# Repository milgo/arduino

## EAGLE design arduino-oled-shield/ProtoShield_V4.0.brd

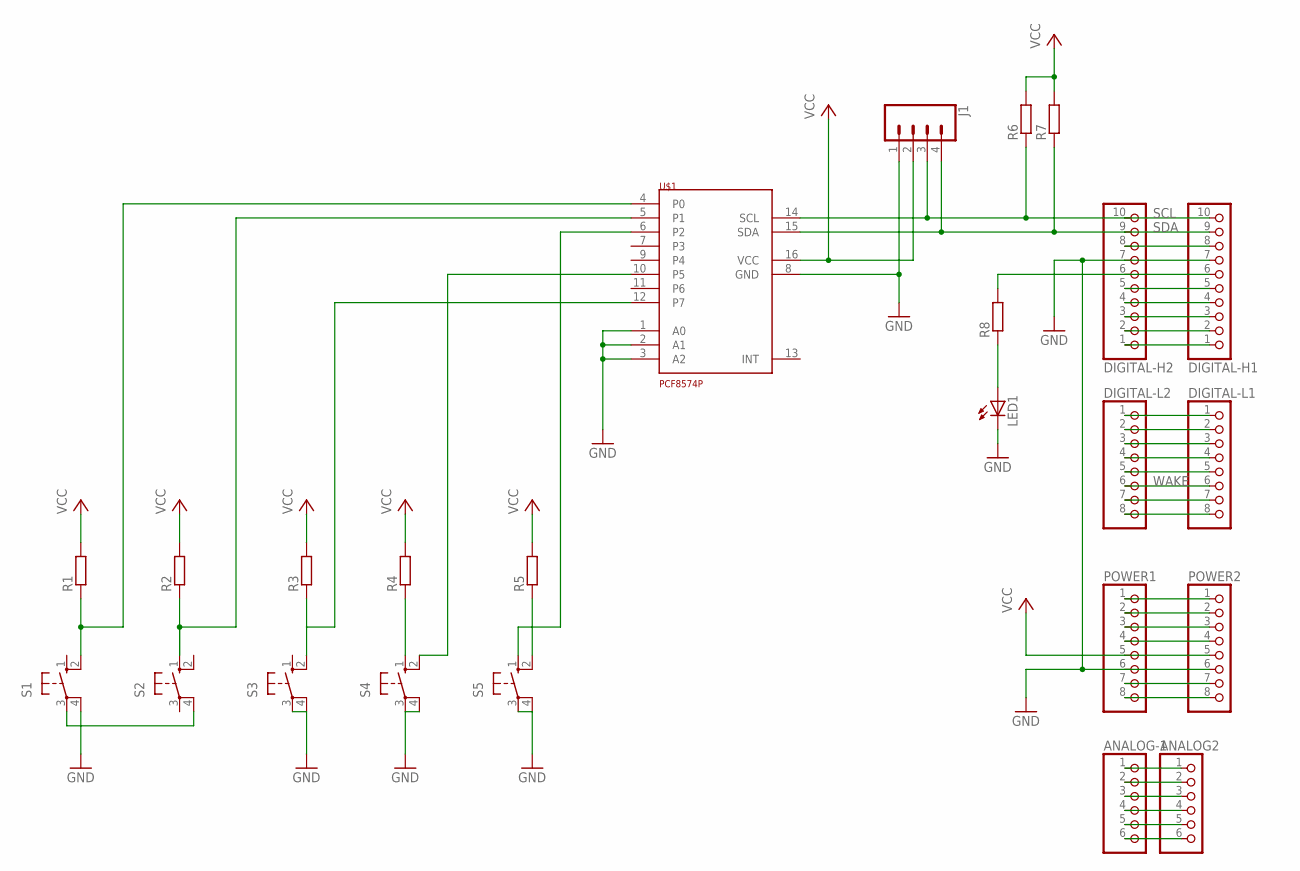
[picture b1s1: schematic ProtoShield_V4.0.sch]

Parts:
ANALOG2: PINHD-1X6; 1X06
ANALOG-1: PINHD-1X6; 1X06
DIGITAL-H1, DIGITAL-H2: PINHD-1X10TH; 1X10-TH
DIGITAL-L1, DIGITAL-L2: PINHD-1X8; 1X08; MPN B67345B0001X087
J1: CONN_04PTH; 1X04
LED1: LED3MM
POWER1, POWER2: PINHD-1X8TH; 1X08-TH
R1, R2, R3, R4, R5, R6, R7, R8: R-EU_0207/10; 0207/10
S1, S2, S3, S4, S5: 10-XX; B3F-10XX
U$1: PCF8574P; DIL16

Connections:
GND: DIGITAL-H1.7, DIGITAL-H2.7, J1.1, LED1.K (C), POWER1.6, POWER2.6, S1.4 (P1), S3.3, S3.4 (P1), S4.3, S4.4 (P1), S5.3, S5.4 (P1), U$1.1 (A0), U$1.2 (A1), U$1.3 (A2), U$1.8 (GND)
IOREF: POWER1.2, POWER2.2
unnamed: DIGITAL-H1.6, DIGITAL-H2.6, R8.2
unnamed: DIGITAL-H1.1, DIGITAL-H2.1
unnamed: DIGITAL-H1.4, DIGITAL-H2.4
unnamed: DIGITAL-H1.5, DIGITAL-H2.5
unnamed: R2.1, S2.1 (S), U$1.5 (P1)
unnamed: DIGITAL-H1.2, DIGITAL-H2.2
unnamed: DIGITAL-H1.3, DIGITAL-H2.3
unnamed: DIGITAL-L1.1, DIGITAL-L2.1
unnamed: DIGITAL-L1.2, DIGITAL-L2.2
unnamed: DIGITAL-L1.3, DIGITAL-L2.3
unnamed: DIGITAL-L1.4, DIGITAL-L2.4
unnamed: DIGITAL-L1.5, DIGITAL-L2.5
unnamed: POWER1.7, POWER2.7
unnamed: DIGITAL-L1.7, DIGITAL-L2.7
unnamed: DIGITAL-L1.8, DIGITAL-L2.8
unnamed: S1.3, S2.4 (P1)
unnamed: R1.1, S1.2 (S1), U$1.4 (P0)
unnamed: ANALOG2.1, ANALOG-1.1
unnamed: ANALOG2.2, ANALOG-1.2
unnamed: ANALOG2.3, ANALOG-1.3
unnamed: ANALOG2.4, ANALOG-1.4
unnamed: ANALOG2.5, ANALOG-1.5
unnamed: ANALOG2.6, ANALOG-1.6
unnamed: LED1.A, R8.1
unnamed: R3.1, S3.2 (S1), U$1.12 (P7)
unnamed: POWER1.3, POWER2.3
unnamed: POWER1.8, POWER2.8
unnamed: R4.1, S4.1 (S)
unnamed: R5.1, S5.2 (S1)
unnamed: POWER1.1, POWER2.1
unnamed: S4.2 (S1), U$1.10 (P5)
unnamed: POWER1.4, POWER2.4
unnamed: S5.1 (S), U$1.6 (P2)
unnamed: DIGITAL-H1.8, DIGITAL-H2.8
SCL: DIGITAL-H1.10, DIGITAL-H2.10, J1.3, R6.1, U$1.14 (SCL)
SDA: DIGITAL-H1.9, DIGITAL-H2.9, J1.4, R7.1, U$1.15 (SDA)
VCC: J1.2, POWER1.5, POWER2.5, R1.2, R2.2, R3.2, R4.2, R5.2, R6.2, R7.2, U$1.16 (VCC)
WAKE: DIGITAL-L1.6, DIGITAL-L2.6

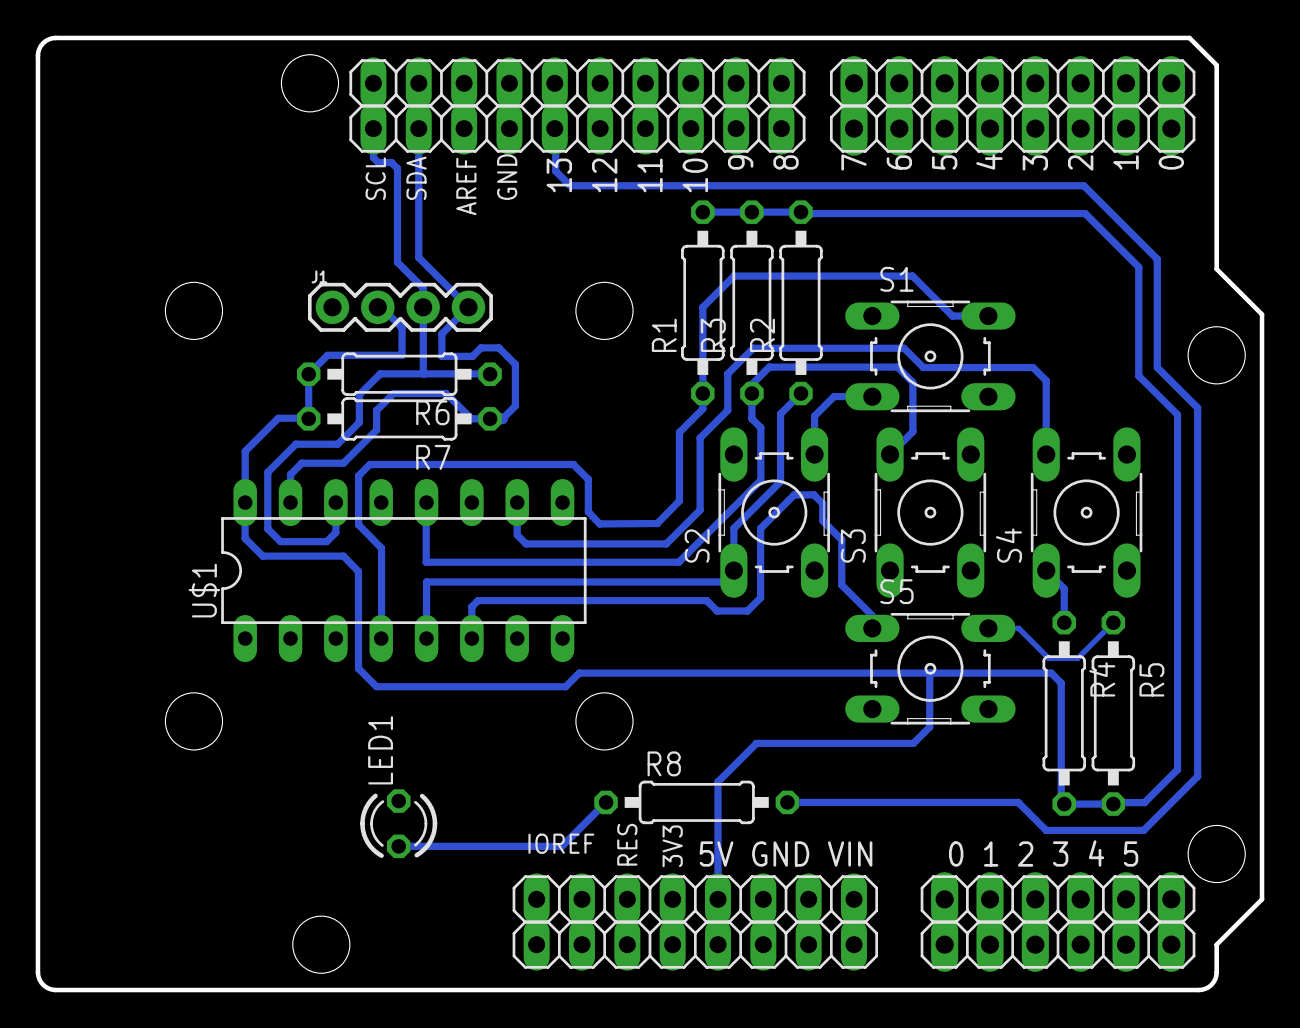
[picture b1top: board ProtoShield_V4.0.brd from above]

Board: 2 copper layers, 68.6 x 53.3 mm, 24 parts (0 on the bottom side), 40 nets.

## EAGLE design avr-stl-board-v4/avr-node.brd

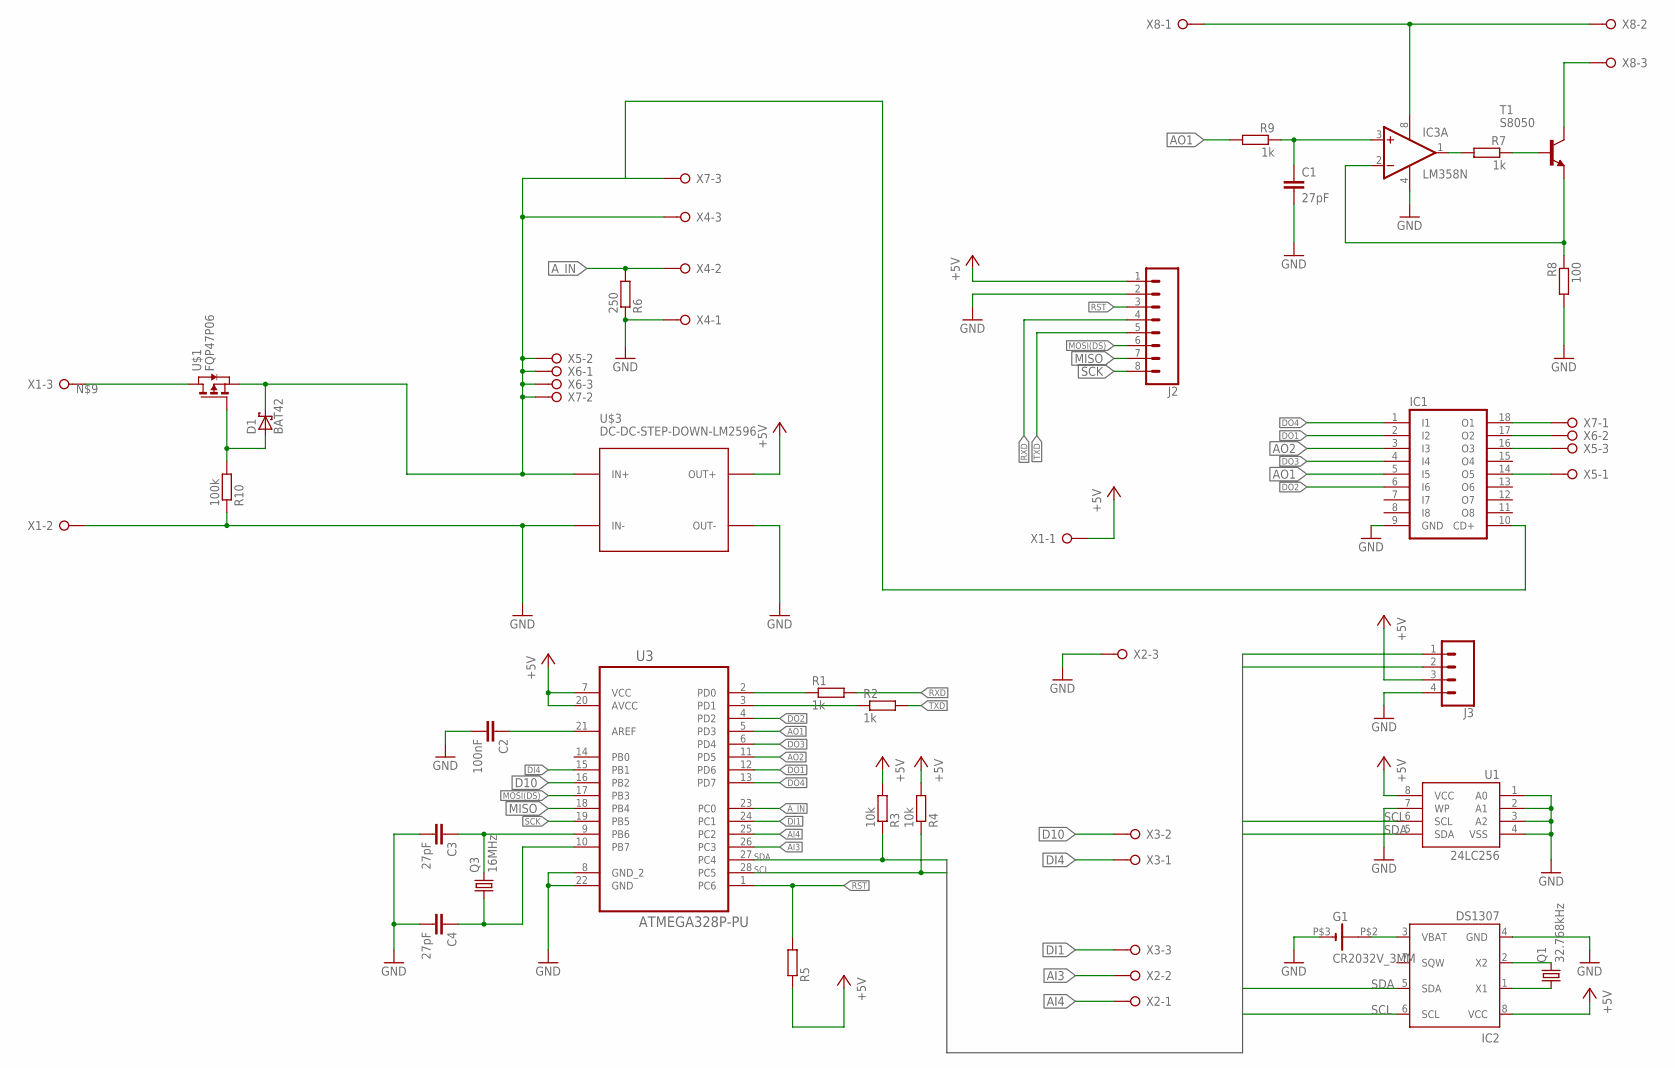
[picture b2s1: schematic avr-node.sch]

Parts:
C1, C3, C4: 27pF; C050-025X075
C2: 100nF; C050-025X075
D1: BAT42; DO35-10
G1: CR2032V_3MM
IC1: ULN2803A; DIL18
IC2: DS1307; DIL08
IC3: LM358N; DIL08
J2: CONN_08LONGPADS; 1X08_LONGPADS
J3: CONN_04PTH; 1X04
Q1: 32.768kHz; TC26V
Q3: 16MHz; HC49U-V
R1, R2, R7, R9: 1k; 0204/7
R3, R4: 10k; 0204/7
R5: R-EU_0204/7; 0204/7
R6: 250; 0204/7
R8: 100; 0204/7
R10: 100k; 0204/7
T1: S8050; TO92L
U1: 24LC256; SO08
U3: ATMEGA328P-PU; DIP254P762X457-28
U$1: FQP47P06; TO220
U$3: DC-DC-STEP-DOWN-LM2596
X1, X2, X3, X4, X5, X6, X7, X8: W237-3E

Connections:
+5V: IC2.8 (VCC), J2.1, J3.3, R3.2, R4.2, R5.1, U1.8 (VCC), U3.7 (VCC), U3.20 (AVCC), U$3.OUT+, X1.1
AI3: U3.26 (PC3), X2.2
AI4: U3.25 (PC2), X2.1
AO1: IC1.5 (I5), R9.2, U3.5 (PD3)
AO2: IC1.3 (I3), U3.11 (PD5)
AO_SUP: IC3.8 (V+), X8.1, X8.2
A_IN: R6.2, U3.23 (PC0), X4.2
D10: U3.16 (PB2), X3.2
DI1: U3.24 (PC1), X3.3
DI4: U3.15 (PB1), X3.1
DO1: IC1.2 (I2), U3.12 (PD6)
DO2: IC1.6 (I6), U3.4 (PD2)
DO3: IC1.4 (I4), U3.6 (PD4)
DO4: IC1.1 (I1), U3.13 (PD7)
GND: C1.2, C2.2, C3.2, C4.2, G1.P$3 (-), IC1.9 (GND), IC2.4 (GND), IC3.4 (V-), J2.2, J3.4, R6.1, R8.2, R10.1, U1.1 (A0), U1.2 (A1), U1.3 (A2), U1.4 (VSS), U1.7 (WP), U3.8 (GND_2), U3.22 (GND), U$3.IN-, U$3.OUT-, X1.2, X2.3, X4.1
MISO: J2.7, U3.18 (PB4)
MOSI(DS): J2.6, U3.17 (PB3)
unnamed: IC3.1 (OUT), R7.2
unnamed: R7.1, T1.2 (B)
unnamed: R1.1, U3.2 (PD0)
unnamed: R2.1, U3.3 (PD1)
unnamed: T1.3 (C), X8.3
unnamed: C2.1, U3.21 (AREF)
unnamed: C3.1, Q3.2, U3.9 (PB6)
unnamed: C4.1, Q3.1, U3.10 (PB7)
unnamed: U$1.2 (D), X1.3
unnamed: IC1.16 (O3), X5.3
unnamed: IC1.17 (O2), X6.2
unnamed: IC1.14 (O5), X5.1
unnamed: IC1.18 (O1), X7.1
unnamed: IC3.2 (-IN), R8.1, T1.1 (E)
unnamed: D1.A, R10.2, U$1.1 (G)
unnamed: C1.1, IC3.3 (+IN), R9.1
unnamed: IC2.2 (X2), Q1.2
unnamed: IC2.1 (X1), Q1.1
unnamed: G1.P$2 (+), IC2.3 (VBAT)
RST: J2.3, R5.2, U3.1 (PC6)
RXD: J2.4, R1.2
SCK: J2.8, U3.19 (PB5)
SCL: IC2.6 (SCL), J3.1, R4.1, U1.6 (SCL), U3.28 (PC5)
SDA: IC2.5 (SDA), J3.2, R3.1, U1.5 (SDA), U3.27 (PC4)
TXD: J2.5, R2.2
V_IN: D1.C, IC1.10 (CD+), U$1.3 (S), U$3.IN+, X4.3, X5.2, X6.1, X6.3, X7.2, X7.3

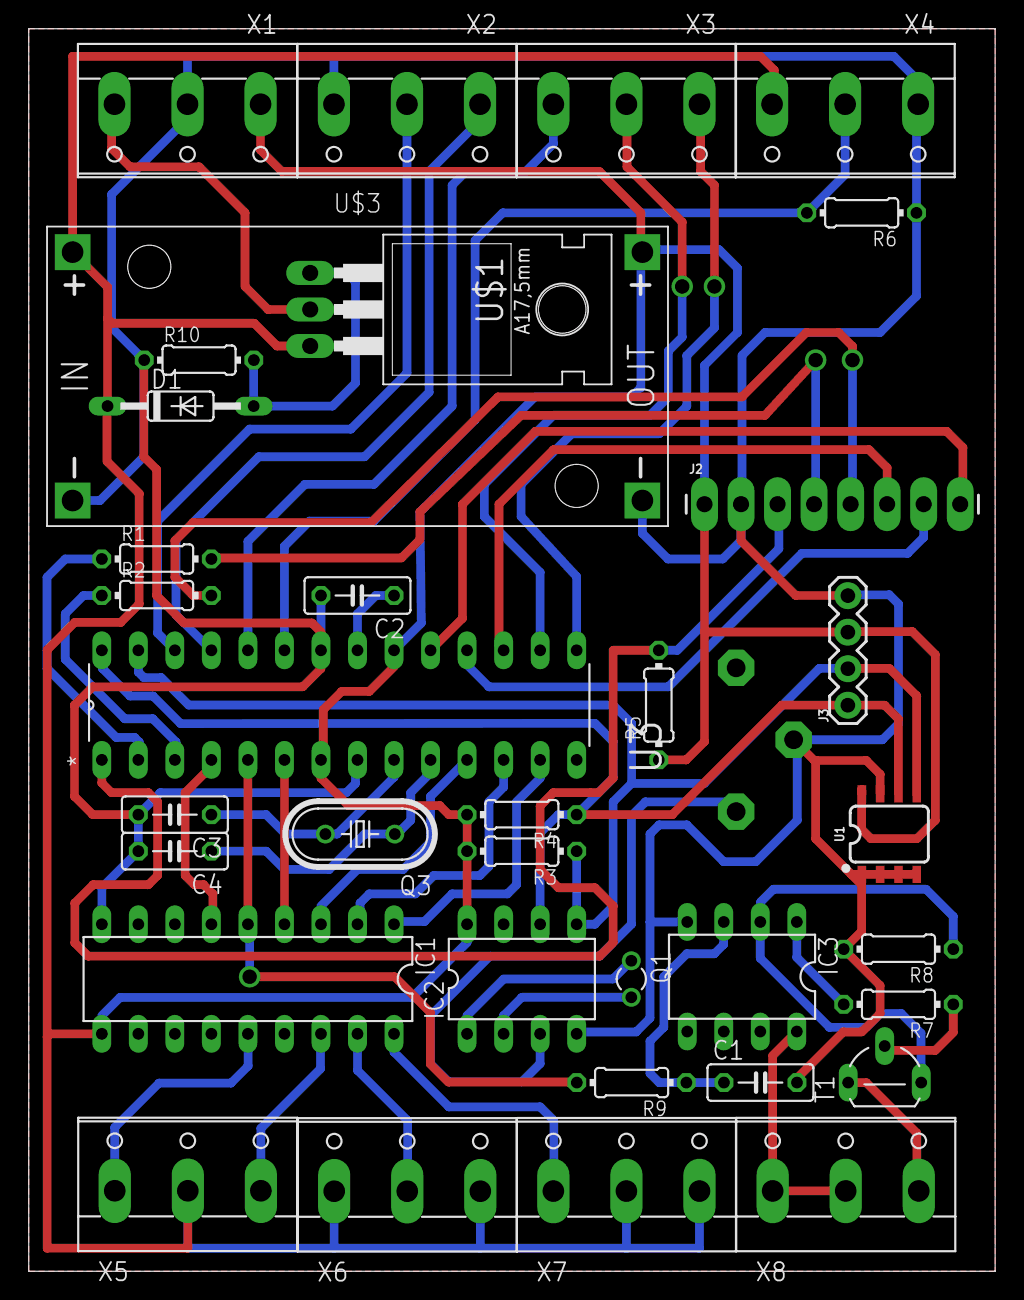
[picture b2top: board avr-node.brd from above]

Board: 2 copper layers, 67.2 x 86.4 mm, 36 parts (0 on the bottom side), 43 nets.

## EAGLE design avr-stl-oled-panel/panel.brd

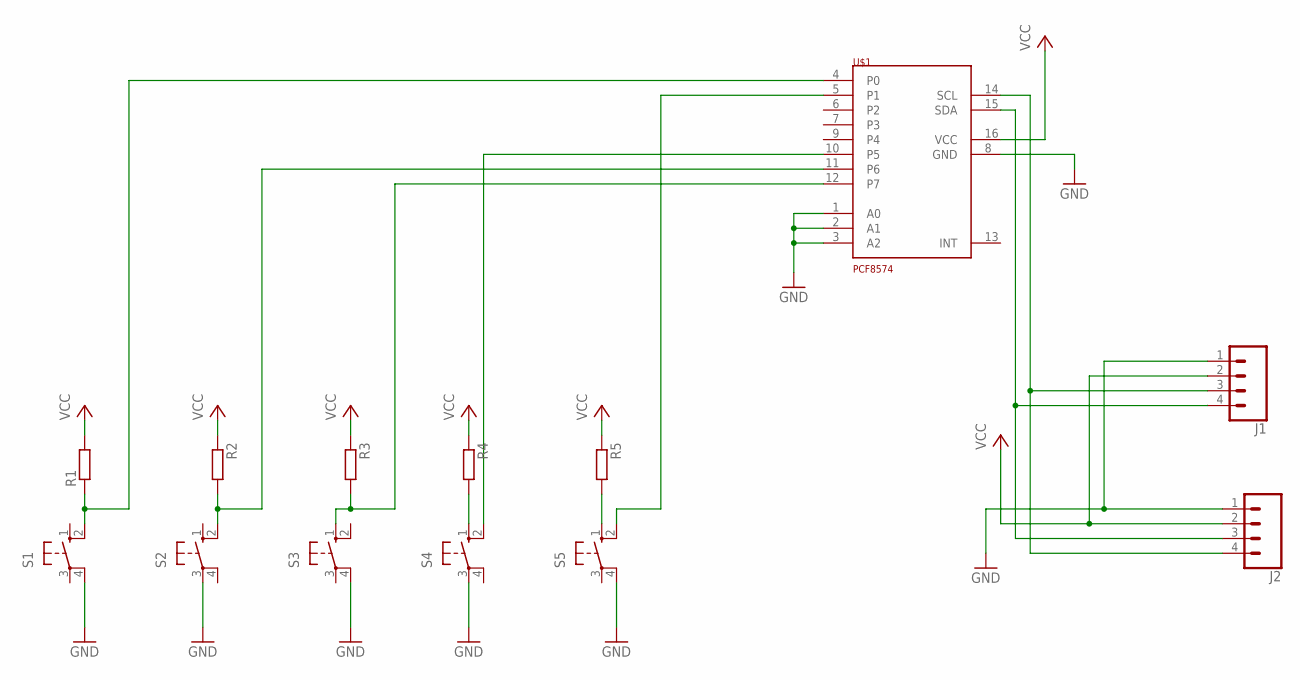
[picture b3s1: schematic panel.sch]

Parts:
J1, J2: CONN_04PTH; 1X04
R1, R2, R3, R4, R5: R-EU_0204/7; 0204/7
S1, S2, S3, S4, S5: 10-XX; B3F-10XX
U$1: PCF8574; SO16(SW)

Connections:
B0: R1.1, S1.2 (S1), U$1.4 (P0)
B1: R2.2, S2.2 (S1), U$1.11 (P6)
B2: R3.2, S3.1 (S), U$1.12 (P7)
B3: S4.2 (S1), U$1.10 (P5)
B4: S5.2 (S1), U$1.5 (P1)
GND: J1.1, J2.1, S1.4 (P1), S2.3, S3.4 (P1), S4.3, S5.4 (P1), U$1.1 (A0), U$1.2 (A1), U$1.3 (A2), U$1.8 (GND)
unnamed: R5.2, S5.1 (S)
unnamed: R4.2, S4.1 (S)
unnamed: J1.4, J2.3, U$1.15 (SDA)
unnamed: J1.3, J2.4, U$1.14 (SCL)
VCC: J1.2, J2.2, R1.2, R2.1, R3.1, R4.1, R5.1, U$1.16 (VCC)

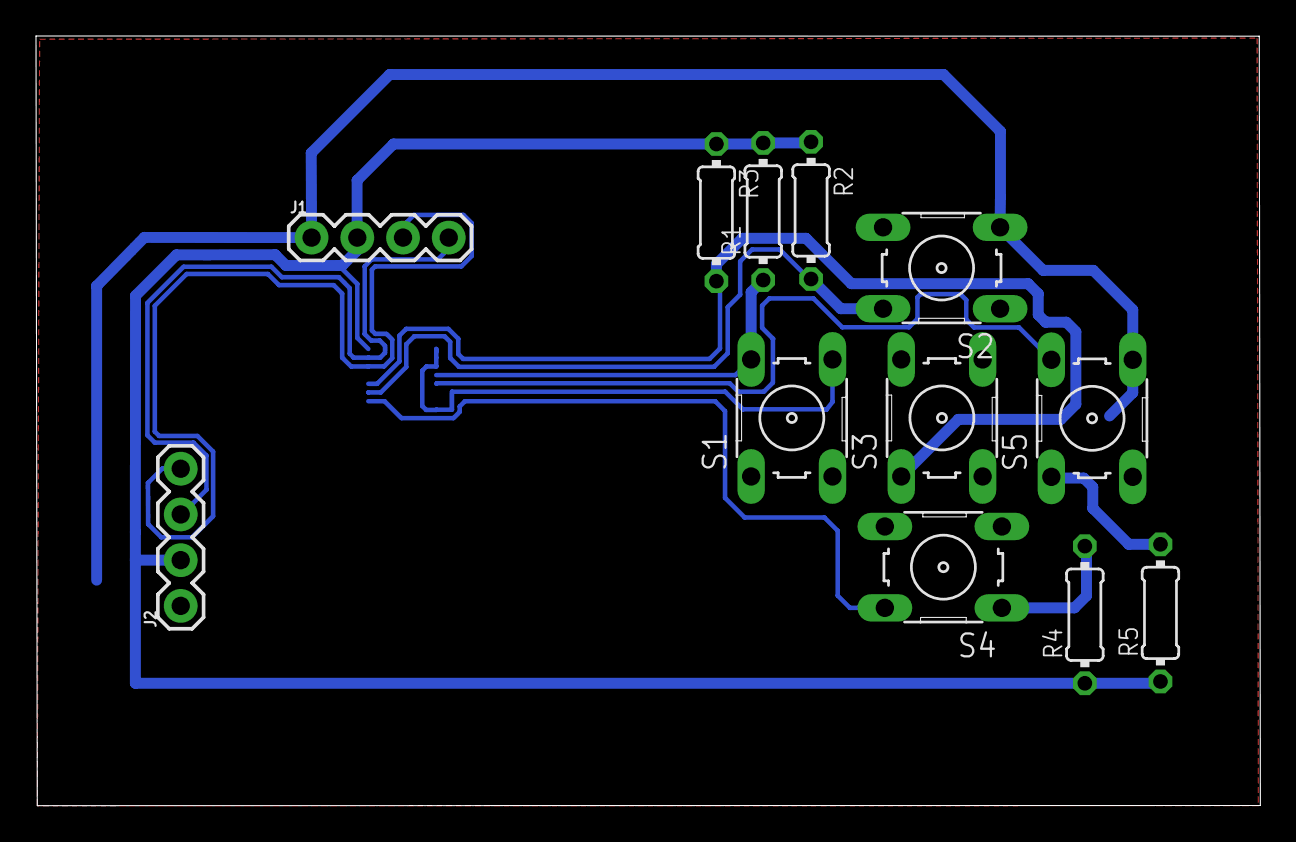
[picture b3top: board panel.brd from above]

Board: 2 copper layers, 68.0 x 42.8 mm, 13 parts (1 on the bottom side), 11 nets.

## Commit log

2021-04-22 two menus and better getButtons function
2021-04-23 single dimention menu array
2021-04-26 walking trought menu in adn out
2021-07-06 implementing function edition
2021-09-24 edit STL program step 1
2021-09-27 moving up and down in editor
2021-09-27 enter value editbox implemented
2021-09-28 advanced enter value editbox
2021-09-29 one show menu function
2021-09-29 show menu from, to feature
2021-09-29 adding move command group
2021-09-30 display msg in progmem
2021-09-30 mem menu array in progmem
2021-09-30 adding mem menu after command
2021-10-01 adding input restriction detection
2021-10-01 enter value based on mem
2021-10-01 adding new program lines
2021-10-01 adding edit menu
2021-10-01 insert, edit, remove program lines
2021-10-18 int uint command mem problem solved
2021-10-19 separating stl interpreter code
2021-10-19 separating gui
2021-10-19 PS and PC separation
2021-10-19 running program and basic testing
2021-10-20 mem organisation, assigning buttonds to I0, led to Q0.5
2021-10-21 always run, enter menu on startup, implementing some functions
2021-10-21 adding input PIND at I0, adding fp and fn basic func
2021-10-22 saving before trying new approach
2021-11-03 new way of handling memory and instructions
2021-11-03 additional validation step (less then checking)
2021-11-04 changing some names, excluding constant from load operation
2021-11-05 load and transfer instructions
2021-11-08 adding sp and se instructions
2021-11-08 adding ss and sf instructions
2021-11-09 buttons are now in input memory area
2021-11-10 m0 fixed timers
2021-11-10 adding counter operations (not tested)
2021-11-16 implementing afterFirstScan
2021-11-16 single operand instructions not inserting bugfix
2021-11-17 implementing aritmetic operations
2021-11-17 small bugfix involving constant aquiring
2021-11-17 real operators bugfixed
2021-11-18 implementing compare operations
2021-11-18 implementing jump instructions and some optimalisations
2021-11-19 instruction and memory optimalisation
2021-11-19 writing and reading program to eeprom
2021-11-19 displaying running indication
2021-11-22 detecting if program changed
2021-11-23 displaying values on oled screen
2021-11-24 accepting commands from serial input
2021-11-25 accepting commands from serial input (echo instruction)
2021-12-02 changing button ids for new board
2021-12-02 adding schematics and boards
2021-12-06 adjusting oled position
2021-12-09 new I/O setup
2021-12-09 changing oled panel chip to smd
2021-12-09 set/get date operations
2021-12-27 adding bit, byte, word persistant commands
2021-12-29 extract params, retriving persistant data before run
2021-12-29 implementing screensaver
2021-12-29 exit running program button combination
2021-12-29 run program after powerup
2022-01-04 arduino oled shield
2022-01-04 adding gitignore
2022-01-04 making changes for arduino
2022-01-04 adding descriptions to commands and memory
2022-01-05 check EEPROM on first run, clear mem on restart, enter value without converting from numerical
2022-01-05 shorter descriptions
2022-01-05 removing timer from few basic commands
2022-01-10 moving things around
2022-01-10 arduino compatible inputs/outputs
2022-01-10 moving stuff around
2022-01-10 adding new value aquire messages
2022-01-12 fixing bugs
2022-01-12 Save, discard, cancel programming eeprom
2022-01-12 erasing local program message
2022-01-18 slow getButtonsNoneBlocking fixed, read analog only when used, popFromACC
2022-01-18 adding run menu
2022-01-19 Create LICENSE
2022-01-19 removing old comments
2022-02-04 oled shield update
2022-02-15 board signal clearance fix

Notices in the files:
parts and their libraries:
SparkFun-Connectors: Licensing: Creative Commons ShareAlike 4.0 International - https://creativecommons.org/licenses/by-sa/4.0
diy-modules: Released under the Creative Commons Attribution 4.0 International License: http://creativecommons.org/licenses/by/4.0
